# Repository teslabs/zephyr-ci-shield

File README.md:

# Zephyr CI Test Shield

This repository contains the board design files for the Zephyr CI Test Shield.
This board is a clone of the ARM mbed CI test shield.

## What is included

* KiCad (5.x) schematic and board files
* Part numbers for JLCPCB assembly (only SMD parts)
* Part numbers from Mouser
* For every revision:
  - Schematic PDF
  - GERBER files
  - BOM and assembly files for JLCPCB
  - Interactive HTML BOM

## Features

* Arduino R3 shield format
* microSD card slot to test SPI
* Resistor star network to test ADC
* EEPROM and temperature sensor to test I2C, EEPROM drivers and sensor drivers
* Loopback pins to test digital inputs, outputs, interrupts, PWM...
* Multiple accessible test points

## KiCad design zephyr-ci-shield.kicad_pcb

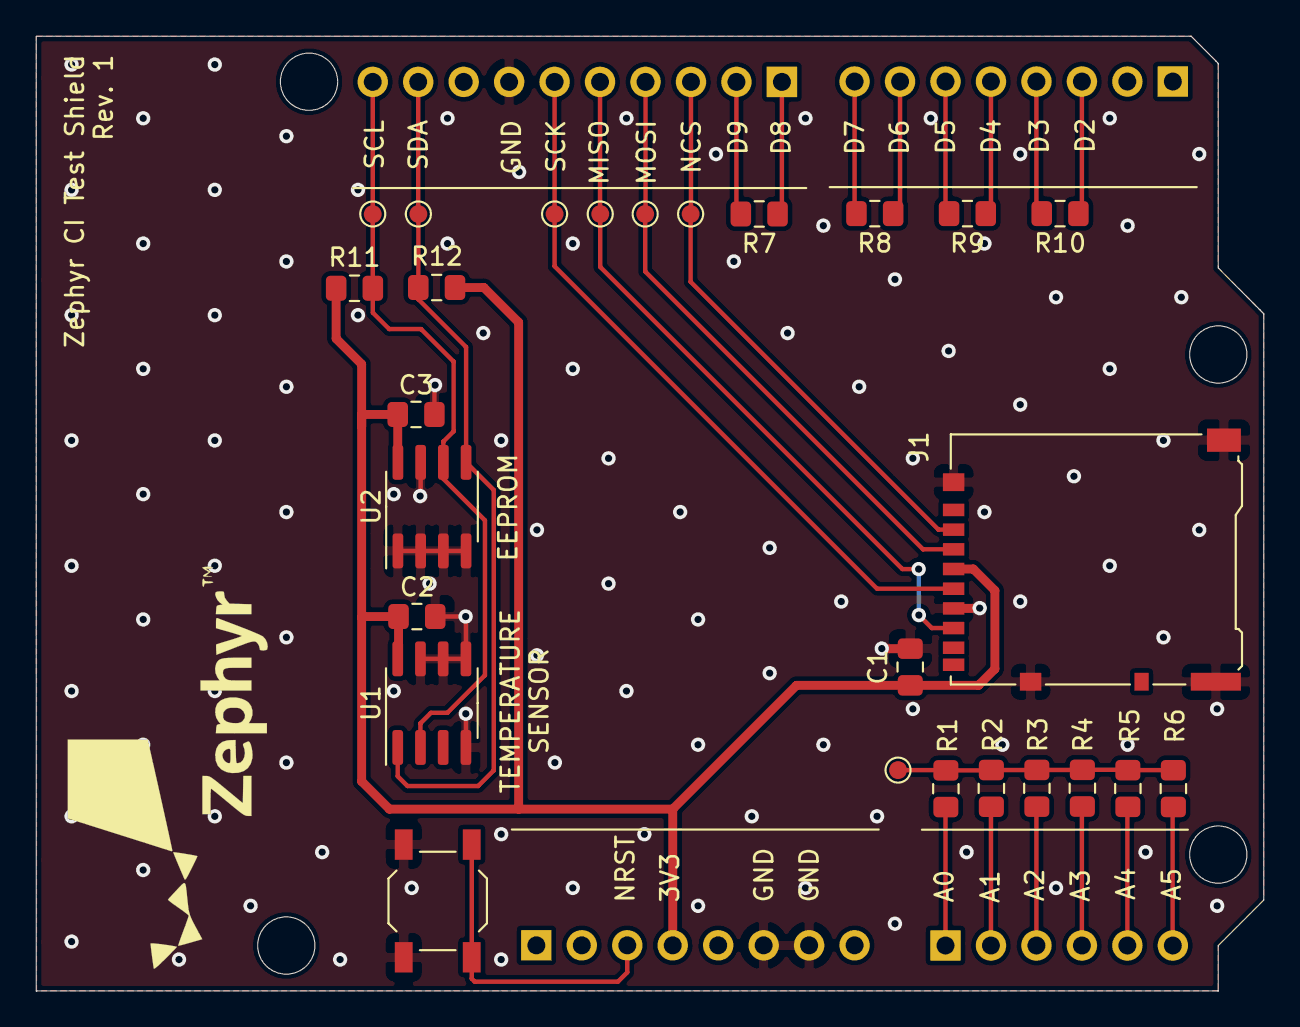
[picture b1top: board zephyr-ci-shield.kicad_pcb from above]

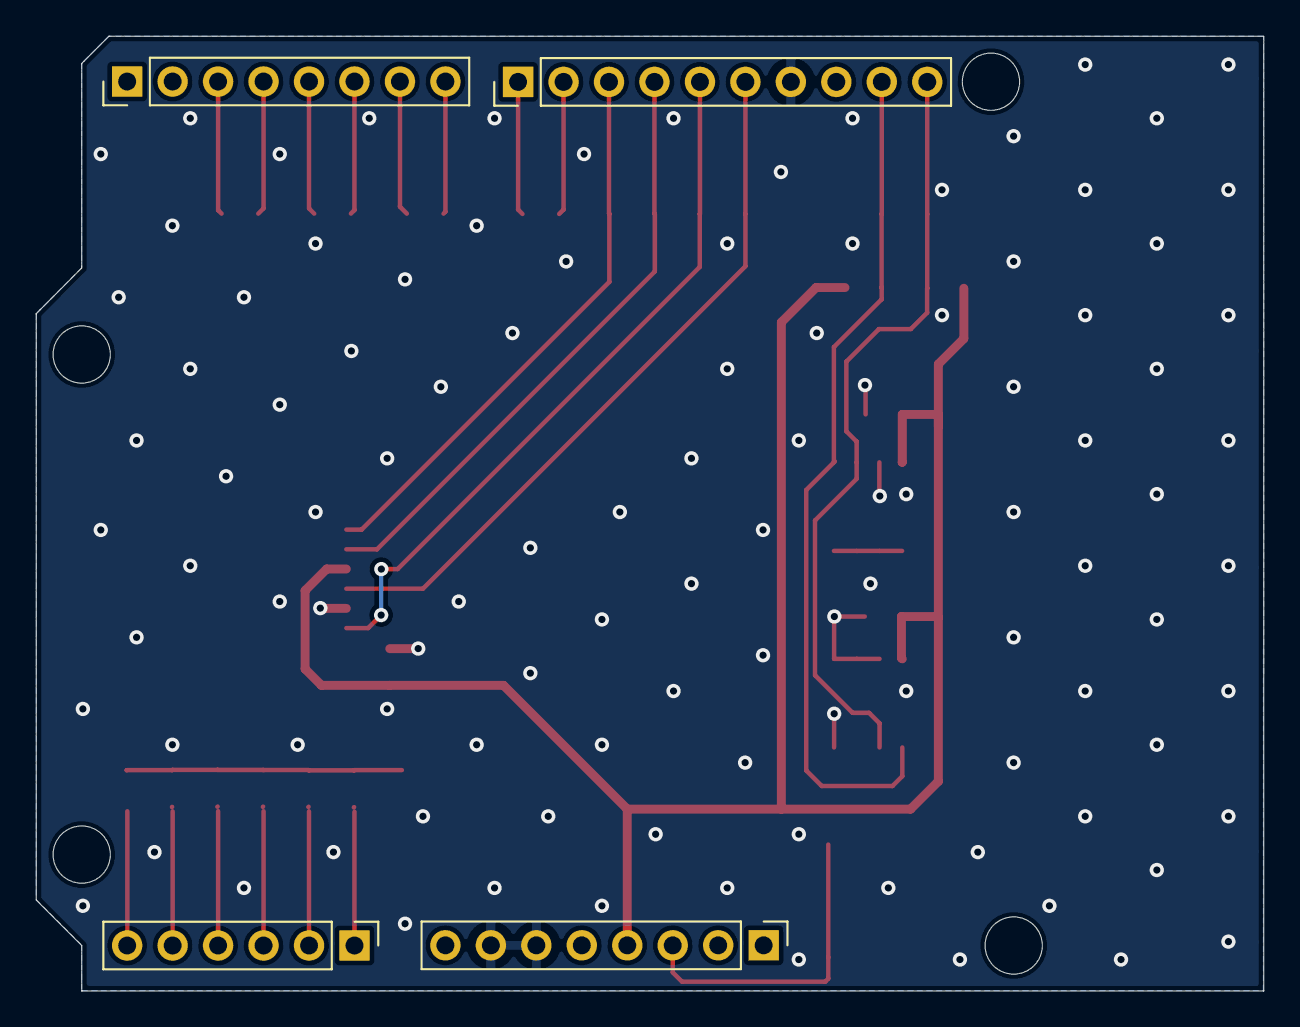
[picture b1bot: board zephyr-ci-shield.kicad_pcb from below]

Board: 2 copper layers, 68.6 x 53.3 mm, 34 parts (4 on the bottom side), 24 nets.

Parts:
C1, C2, C3: 100nF; C_0805_2012Metric_Pad1.15x1.40mm_HandSolder
H1, H2, H3, H4: MountingHole; MountingHole_3.2mm
J1: Micro_SD_Card; microSD_HC_Hirose_DM3AT-SF-PEJM5
J2: CN1; PinHeader_1x08_P2.54mm_Vertical
J3: CN2; PinHeader_1x06_P2.54mm_Vertical
J4: CN4; PinHeader_1x10_P2.54mm_Vertical
J5: CN3; PinHeader_1x08_P2.54mm_Vertical
R1, R2, R3, R4, R5, R6: 10K; R_0805_2012Metric_Pad1.15x1.40mm_HandSolder
R7, R8, R9, R10: 0; R_0805_2012Metric_Pad1.15x1.40mm_HandSolder
R11, R12: 4.7K; R_0805_2012Metric_Pad1.15x1.40mm_HandSolder
SW1: RESET; SW_SPST_TL3342
TP1: AVAL; TestPoint_Pad_D1.0mm
TP2: SCK; TestPoint_Pad_D1.0mm
TP3: MISO; TestPoint_Pad_D1.0mm
TP4: SCL; TestPoint_Pad_D1.0mm
TP5: MOSI; TestPoint_Pad_D1.0mm
TP6: SDA; TestPoint_Pad_D1.0mm
TP7: NCS; TestPoint_Pad_D1.0mm
U1: LM75B; SOIC-8_3.9x4.9mm_P1.27mm
U2: 24LC256; SOIC-8_3.9x4.9mm_P1.27mm

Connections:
+3V3: C1.2, C2.2, C3.1, J1.4, J2.4, R11.1, R12.1, U1.8, U2.8
/MISO: J1.7, J4.5, TP3.1
/MOSI: J1.3, J4.4, TP5.1
/NCS: J1.2, J4.3, TP7.1
/SCK: J1.5, J4.6, TP2.1
/SCL: J4.10, R11.2, TP4.1, U1.2, U2.6
/SDA: J4.9, R12.2, TP6.1, U1.1, U2.5
GND: C1.1, C2.1, C3.2, J1.6, J1.11, J2.6, J2.7, J4.7, SW1.2, U1.4, U1.5, U1.6, U1.7, U2.1, U2.2, U2.3, U2.4, U2.7
unnamed: J2.3, SW1.1
unnamed: J3.1, R1.2
unnamed: J3.2, R2.2
unnamed: J3.3, R3.2
unnamed: J3.4, R4.2
unnamed: J3.5, R5.2
unnamed: J3.6, R6.2
unnamed: J4.1, R7.1
unnamed: J4.2, R7.2
unnamed: J5.3, R10.1
unnamed: J5.4, R10.2
unnamed: J5.5, R9.1
unnamed: J5.6, R9.2
unnamed: J5.7, R8.1
unnamed: J5.8, R8.2
unnamed: R1.1, R2.1, R3.1, R4.1, R5.1, R6.1, TP1.1

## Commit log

2020-08-28 Add LICENSE
